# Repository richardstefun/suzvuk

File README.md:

# SUZVUK opensource repo

This repo contains all of my opensource synth projects

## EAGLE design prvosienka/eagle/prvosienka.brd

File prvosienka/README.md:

# Prvosienka

*Eurorack Busboard*

Prvosienka is an eurorack standard compatible busboard capable of providing power for up to 16 modules.
The board can be mounted using standoffs by 17 different screw holes, with 3mm diameter holes. 

## Schematic diagram

**Features**

Board contains a **LF50AB** very low-dropout 5V voltage regulator, which can be used to provide 5V rail, if your PSU does not provide it. You should also cross the "**5V?**" header to enable the regulator.
There are also three **TE-5** type THT fuses. The recommended fuse amperage is *3.15A*, but it's up to you to choose. If you decide to omit it, a thick wire should be used to connect both terminals.
If you want to split the GATE and CV buses, do not install a jumper in the "**Join?**" terminals.
Board also provides polarity markings for flat cables, because it's designed to use pin headers rather than plastic pin header connectors, to save cost and space.

**Capacitors**

This board is designed for **0603** ceramic capacitors (decoupling) and **B-Type** package electrolytic capacitors. It's up to you to choose their values, but recommended to use **100nF** for decoupling and **10uF 25V** for all electrolytic capacitors. You don't need to populate all pads with decoupling capacitors. Recommended placements are next to connectors on edges of board, and **WAGO 256** connectors. The board works fine without any capacitors, you should only add them if you're experiencing any interference

**Power indicator**

In the middle of the board is a small power indicator that uses 3 LEDs to determine if all power rails do have voltage on them. Those LEDs need 2 kinds of resistors. For **12V** and **-12V** use **1k 0603** resistor, **330R 0603** fits the **5V** rail nicely. You should use an **0603 LED** **10**-**20mA** **LED**. This feature is also optional. 

**! Always check LED's and electrolytic capacitor polarity before soldering**

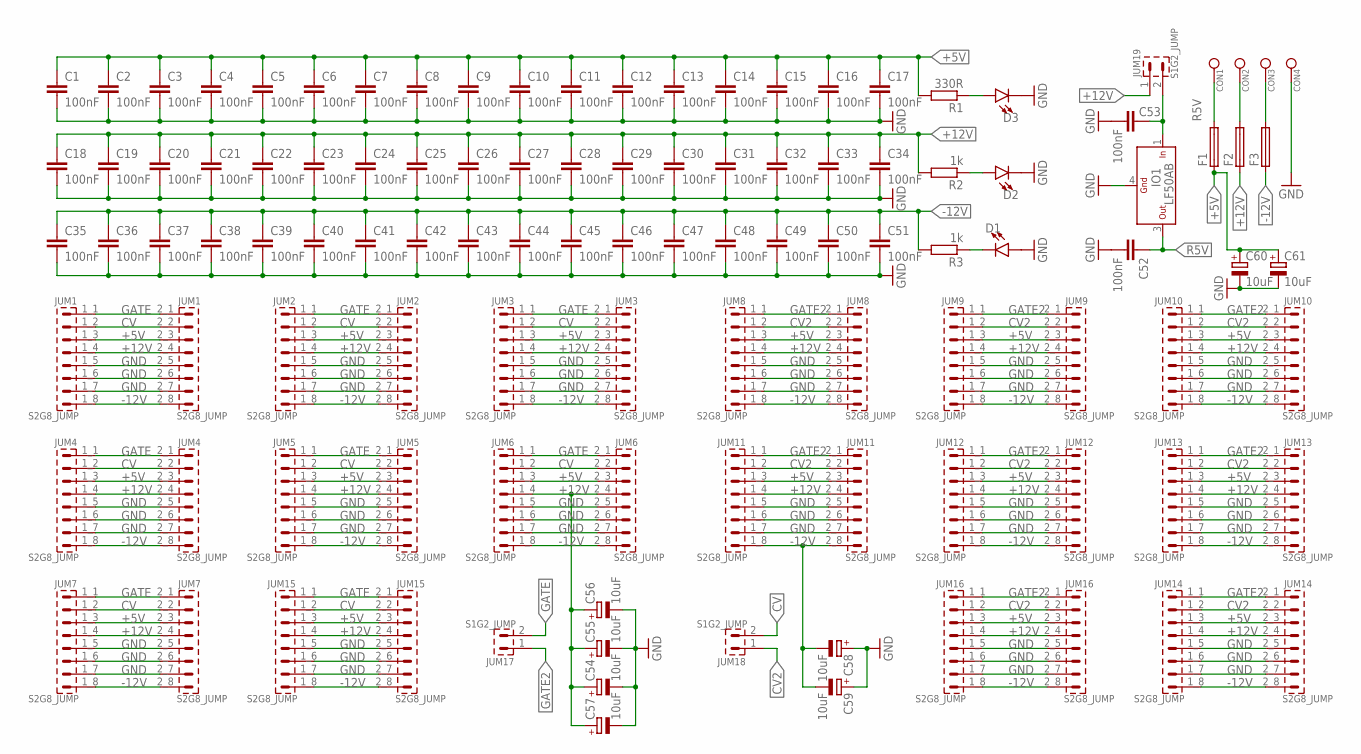
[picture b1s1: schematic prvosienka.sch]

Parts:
C1, C2, C3, C4, C5, C6, C7, C8, C9, C10, C11, C12, C13, C14, C15, C16, C17, C18, C19, C20, C21, C22, C23, C24, C25, C26, C27, C28, C29, C30, C31, C32, C33, C34, C35, C36, C37, C38, C39, C40, C41, C42, C43, C44, C45, C46, C47, C48, C49, C50, C51, C52, C53: 100nF; C0603K
C54, C55, C56, C57, C58, C59, C60, C61: 10uF; PANASONIC_B
CON1, CON2, CON3, CON4: WAGO256
D1, D2, D3: LED0603; LED-0603
F1, F2, F3: TE5
IO1: LF50AB; DPAK
JUM1, JUM2, JUM3, JUM4, JUM5, JUM6, JUM7, JUM8, JUM9, JUM10, JUM11, JUM12, JUM13, JUM14, JUM15, JUM16: S2G8_JUMP; S2G8_JUM
JUM17, JUM18, JUM19: S1G2_JUMP; S1G2_JUM
R1: 330R; R0603
R2, R3: 1k; R0603

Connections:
+5V: C1.1, C2.1, C3.1, C4.1, C5.1, C6.1, C7.1, C8.1, C9.1, C10.1, C11.1, C12.1, C13.1, C14.1, C15.1, C16.1, C17.1, C60.+, C61.+, F1.1, JUM1.1_3 (3), JUM1.2_3 (3), JUM2.1_3 (3), JUM2.2_3 (3), JUM3.1_3 (3), JUM3.2_3 (3), JUM4.1_3 (3), JUM4.2_3 (3), JUM5.1_3 (3), JUM5.2_3 (3), JUM6.1_3 (3), JUM6.2_3 (3), JUM7.1_3 (3), JUM7.2_3 (3), JUM8.1_3 (3), JUM8.2_3 (3), JUM9.1_3 (3), JUM9.2_3 (3), JUM10.1_3 (3), JUM10.2_3 (3), JUM11.1_3 (3), JUM11.2_3 (3), JUM12.1_3 (3), JUM12.2_3 (3), JUM13.1_3 (3), JUM13.2_3 (3), JUM14.1_3 (3), JUM14.2_3 (3), JUM15.1_3 (3), JUM15.2_3 (3), JUM16.1_3 (3), JUM16.2_3 (3), R1.2
+12V: C18.1, C19.1, C20.1, C21.1, C22.1, C23.1, C24.1, C25.1, C26.1, C27.1, C28.1, C29.1, C30.1, C31.1, C32.1, C33.1, C34.1, C54.+, C55.+, C56.+, C57.+, F2.1, JUM1.1_4 (4), JUM1.2_4 (4), JUM2.1_4 (4), JUM2.2_4 (4), JUM3.1_4 (4), JUM3.2_4 (4), JUM4.1_4 (4), JUM4.2_4 (4), JUM5.1_4 (4), JUM5.2_4 (4), JUM6.1_4 (4), JUM6.2_4 (4), JUM7.1_4 (4), JUM7.2_4 (4), JUM8.1_4 (4), JUM8.2_4 (4), JUM9.1_4 (4), JUM9.2_4 (4), JUM10.1_4 (4), JUM10.2_4 (4), JUM11.1_4 (4), JUM11.2_4 (4), JUM12.1_4 (4), JUM12.2_4 (4), JUM13.1_4 (4), JUM13.2_4 (4), JUM14.1_4 (4), JUM14.2_4 (4), JUM15.1_4 (4), JUM15.2_4 (4), JUM16.1_4 (4), JUM16.2_4 (4), JUM19.1, R2.2
-12V: C35.1, C36.1, C37.1, C38.1, C39.1, C40.1, C41.1, C42.1, C43.1, C44.1, C45.1, C46.1, C47.1, C48.1, C49.1, C50.1, C51.1, C58.-, C59.-, F3.1, JUM1.1_8 (8), JUM1.2_8 (8), JUM2.1_8 (8), JUM2.2_8 (8), JUM3.1_8 (8), JUM3.2_8 (8), JUM4.1_8 (8), JUM4.2_8 (8), JUM5.1_8 (8), JUM5.2_8 (8), JUM6.1_8 (8), JUM6.2_8 (8), JUM7.1_8 (8), JUM7.2_8 (8), JUM8.1_8 (8), JUM8.2_8 (8), JUM9.1_8 (8), JUM9.2_8 (8), JUM10.1_8 (8), JUM10.2_8 (8), JUM11.1_8 (8), JUM11.2_8 (8), JUM12.1_8 (8), JUM12.2_8 (8), JUM13.1_8 (8), JUM13.2_8 (8), JUM14.1_8 (8), JUM14.2_8 (8), JUM15.1_8 (8), JUM15.2_8 (8), JUM16.1_8 (8), JUM16.2_8 (8), R3.2
CV: JUM1.1_2 (2), JUM1.2_2 (2), JUM2.1_2 (2), JUM2.2_2 (2), JUM3.1_2 (2), JUM3.2_2 (2), JUM4.1_2 (2), JUM4.2_2 (2), JUM5.1_2 (2), JUM5.2_2 (2), JUM6.1_2 (2), JUM6.2_2 (2), JUM7.1_2 (2), JUM7.2_2 (2), JUM15.1_2 (2), JUM15.2_2 (2), JUM18.2
CV2: JUM8.1_2 (2), JUM8.2_2 (2), JUM9.1_2 (2), JUM9.2_2 (2), JUM10.1_2 (2), JUM10.2_2 (2), JUM11.1_2 (2), JUM11.2_2 (2), JUM12.1_2 (2), JUM12.2_2 (2), JUM13.1_2 (2), JUM13.2_2 (2), JUM14.1_2 (2), JUM14.2_2 (2), JUM16.1_2 (2), JUM16.2_2 (2), JUM18.1
GATE: JUM1.1_1 (1), JUM1.2_1 (1), JUM2.1_1 (1), JUM2.2_1 (1), JUM3.1_1 (1), JUM3.2_1 (1), JUM4.1_1 (1), JUM4.2_1 (1), JUM5.1_1 (1), JUM5.2_1 (1), JUM6.1_1 (1), JUM6.2_1 (1), JUM7.1_1 (1), JUM7.2_1 (1), JUM15.1_1 (1), JUM15.2_1 (1), JUM17.2
GATE2: JUM8.1_1 (1), JUM8.2_1 (1), JUM9.1_1 (1), JUM9.2_1 (1), JUM10.1_1 (1), JUM10.2_1 (1), JUM11.1_1 (1), JUM11.2_1 (1), JUM12.1_1 (1), JUM12.2_1 (1), JUM13.1_1 (1), JUM13.2_1 (1), JUM14.1_1 (1), JUM14.2_1 (1), JUM16.1_1 (1), JUM16.2_1 (1), JUM17.1
GND: C1.2, C2.2, C3.2, C4.2, C5.2, C6.2, C7.2, C8.2, C9.2, C10.2, C11.2, C12.2, C13.2, C14.2, C15.2, C16.2, C17.2, C18.2, C19.2, C20.2, C21.2, C22.2, C23.2, C24.2, C25.2, C26.2, C27.2, C28.2, C29.2, C30.2, C31.2, C32.2, C33.2, C34.2, C35.2, C36.2, C37.2, C38.2, C39.2, C40.2, C41.2, C42.2, C43.2, C44.2, C45.2, C46.2, C47.2, C48.2, C49.2, C50.2, C51.2, C52.2, C53.2, C54.-, C55.-, C56.-, C57.-, C58.+, C59.+, C60.-, C61.-, CON4.1, D1.A, D2.C, D3.C, IO1.4 (GND), JUM1.1_5 (5), JUM1.1_6 (6), JUM1.1_7 (7), JUM1.2_5 (5), JUM1.2_6 (6), JUM1.2_7 (7), JUM2.1_5 (5), JUM2.1_6 (6), JUM2.1_7 (7), JUM2.2_5 (5), JUM2.2_6 (6), JUM2.2_7 (7), JUM3.1_5 (5), JUM3.1_6 (6), JUM3.1_7 (7), JUM3.2_5 (5), JUM3.2_6 (6), JUM3.2_7 (7), JUM4.1_5 (5), JUM4.1_6 (6), JUM4.1_7 (7), JUM4.2_5 (5), JUM4.2_6 (6), JUM4.2_7 (7), JUM5.1_5 (5), JUM5.1_6 (6), JUM5.1_7 (7), JUM5.2_5 (5), JUM5.2_6 (6), JUM5.2_7 (7), JUM6.1_5 (5), JUM6.1_6 (6), JUM6.1_7 (7), JUM6.2_5 (5), JUM6.2_6 (6), JUM6.2_7 (7), JUM7.1_5 (5), JUM7.1_6 (6), JUM7.1_7 (7), JUM7.2_5 (5), JUM7.2_6 (6), JUM7.2_7 (7), JUM8.1_5 (5), JUM8.1_6 (6), JUM8.1_7 (7), JUM8.2_5 (5), JUM8.2_6 (6), JUM8.2_7 (7), JUM9.1_5 (5), JUM9.1_6 (6), JUM9.1_7 (7), JUM9.2_5 (5), JUM9.2_6 (6), JUM9.2_7 (7), JUM10.1_5 (5), JUM10.1_6 (6), JUM10.1_7 (7), JUM10.2_5 (5), JUM10.2_6 (6), JUM10.2_7 (7), JUM11.1_5 (5), JUM11.1_6 (6), JUM11.1_7 (7), JUM11.2_5 (5), JUM11.2_6 (6), JUM11.2_7 (7), JUM12.1_5 (5), JUM12.1_6 (6), JUM12.1_7 (7), JUM12.2_5 (5), JUM12.2_6 (6), JUM12.2_7 (7), JUM13.1_5 (5), JUM13.1_6 (6), JUM13.1_7 (7), JUM13.2_5 (5), JUM13.2_6 (6), JUM13.2_7 (7), JUM14.1_5 (5), JUM14.1_6 (6), JUM14.1_7 (7), JUM14.2_5 (5), JUM14.2_6 (6), JUM14.2_7 (7), JUM15.1_5 (5), JUM15.1_6 (6), JUM15.1_7 (7), JUM15.2_5 (5), JUM15.2_6 (6), JUM15.2_7 (7), JUM16.1_5 (5), JUM16.1_6 (6), JUM16.1_7 (7), JUM16.2_5 (5), JUM16.2_6 (6), JUM16.2_7 (7)
unnamed: D3.A, R1.1
unnamed: D2.A, R2.1
unnamed: D1.C, R3.1
unnamed: CON3.1, F3.2
unnamed: CON2.1, F2.2
unnamed: C53.1, IO1.1 (IN), JUM19.2
R5V: C52.1, CON1.1, F1.2, IO1.3 (OUT)

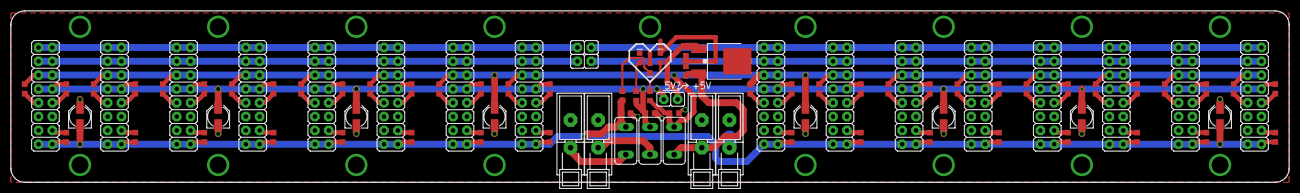
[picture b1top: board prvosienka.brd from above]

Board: 2 copper layers, 234.9 x 31.5 mm, 94 parts (0 on the bottom side), 15 nets.

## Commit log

2020-02-13 eagle files and render
2020-02-13 gitignore update
2020-02-14 led detail
2020-02-14 gerber files
2020-02-14 changed led detail

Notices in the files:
parts and their libraries:
Copyright (C) PaJa 2011-2014
Copyright (C) PaJa 2001-2014
SparkFun-LED: Licensing: Creative Commons ShareAlike 4.0 International - https://creativecommons.org/licenses/by-sa/4.0
